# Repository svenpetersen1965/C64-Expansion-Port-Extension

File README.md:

This is an extension cable thing for the C64 Expansion Port, consisting of two PCBs, one fits into the C64, the other provices an expansion port connector, which are connected via a ribbon cable. 

Rev. 0 of this project is now built and tested. A 25cm ribbon cable is good, a 100cm ribbon cable is too long.

For User Port and Cassette Port Extension Cable see: <a href="https://github.com/svenpetersen1965/Commodore-Port-Breakout">Commodore Port Breakout</a>

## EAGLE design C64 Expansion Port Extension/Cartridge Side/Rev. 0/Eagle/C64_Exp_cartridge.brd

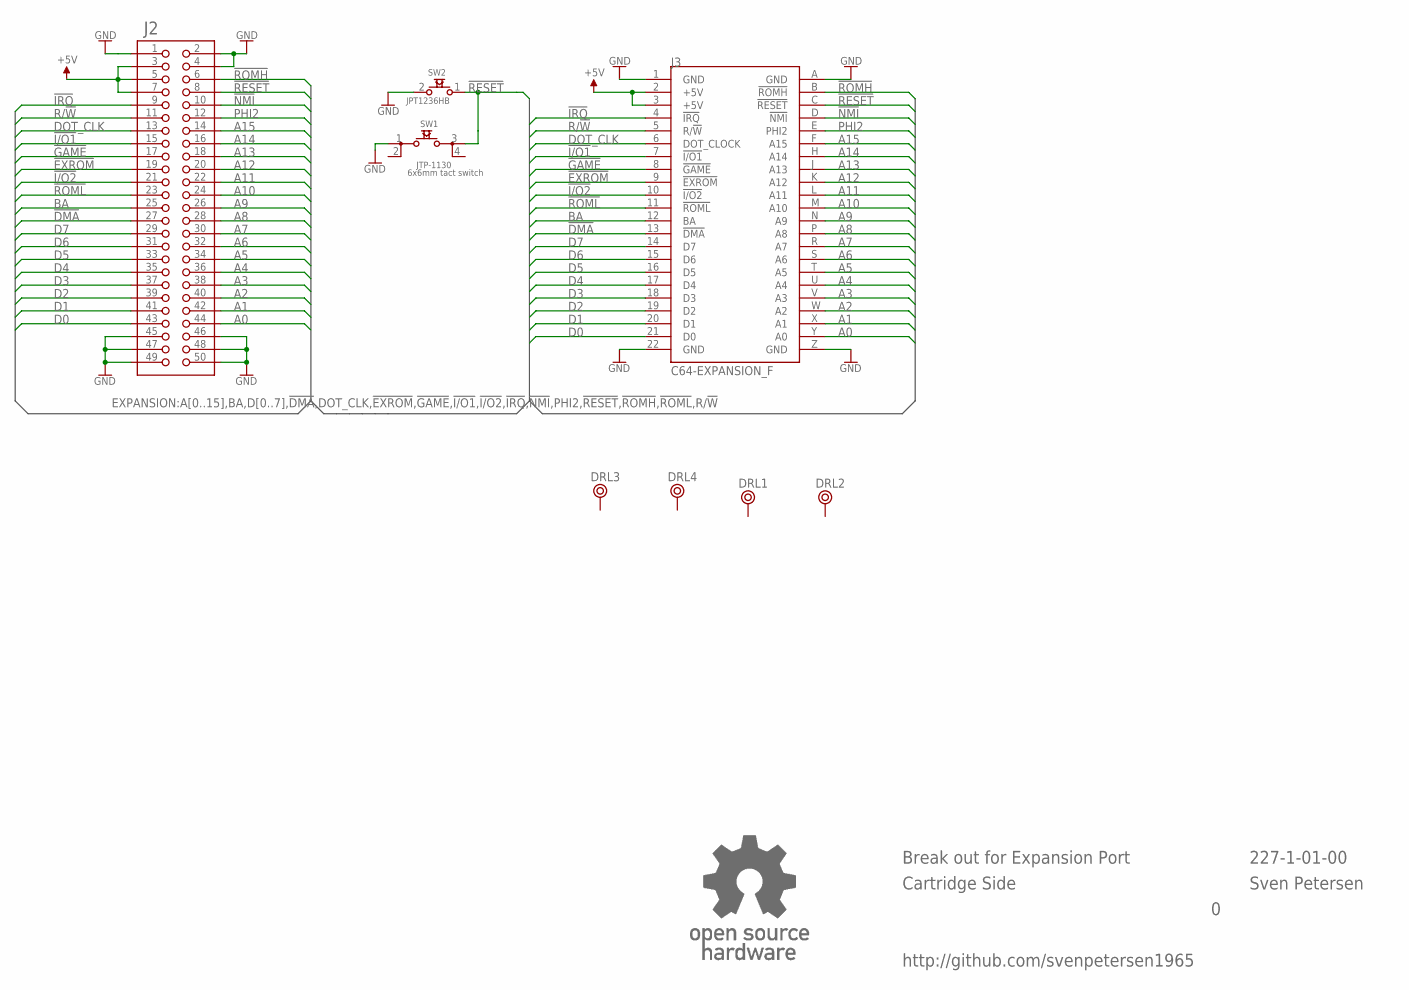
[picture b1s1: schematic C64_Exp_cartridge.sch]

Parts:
DRL1, DRL2, DRL3, DRL4: BOHR3,3
J2: PINHD-2X25BOX; 2X25WV
J3: C64-EXPANSION_F; EXPANSION_OUT
SW1: JTP-1130
SW2: JPT1236HB; JTP_1236HB
U$22: OPEN_SOURCE_HW; OPENHW

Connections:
!DMA: J2.27, J3.13 (!DMA)
!EXROM: J2.19, J3.9 (!EXROM)
!GAME: J2.17, J3.8 (!GAME)
!I/O1: J2.15, J3.7 (!I/O1)
!I/O2: J2.21, J3.10 (!I/O2)
!IRQ: J2.9, J3.4 (!IRQ)
!NMI: J2.10, J3.D (!NMI)
!RESET: J2.8, J3.C (!RESET), SW1.3, SW2.1
!ROMH: J2.6, J3.B (!ROMH)
!ROML: J2.23, J3.11 (!ROML)
+5V: J2.3, J2.5, J2.7, J3.2 (+5V), J3.3 (+5V)
A0: J2.44, J3.Y (A0)
A1: J2.42, J3.X (A1)
A2: J2.40, J3.W (A2)
A3: J2.38, J3.V (A3)
A4: J2.36, J3.U (A4)
A5: J2.34, J3.T (A5)
A6: J2.32, J3.S (A6)
A7: J2.30, J3.R (A7)
A8: J2.28, J3.P (A8)
A9: J2.26, J3.N (A9)
A10: J2.24, J3.M (A10)
A11: J2.22, J3.L (A11)
A12: J2.20, J3.K (A12)
A13: J2.18, J3.J (A13)
A14: J2.16, J3.H (A14)
A15: J2.14, J3.F (A15)
BA: J2.25, J3.12 (BA)
D0: J2.43, J3.21 (D0)
D1: J2.41, J3.20 (D1)
D2: J2.39, J3.19 (D2)
D3: J2.37, J3.18 (D3)
D4: J2.35, J3.17 (D4)
D5: J2.33, J3.16 (D5)
D6: J2.31, J3.15 (D6)
D7: J2.29, J3.14 (D7)
DOT_CLK: J2.13, J3.6 (DOT_CLOCK)
GND: J2.1, J2.2, J2.4, J2.45, J2.46, J2.47, J2.48, J2.49, J2.50, J3.1 (GND), J3.22 (GND), J3.A (GND), J3.Z (GND), SW1.1, SW2.2
PHI2: J2.12, J3.E (PHI2)
R/!W: J2.11, J3.5 (R/!W)

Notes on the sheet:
Sven Petersen
227-1-01-00
http://github.com/svenpetersen1965
6x6mm tact switch
Break out for Expansion Port
Cartridge Side

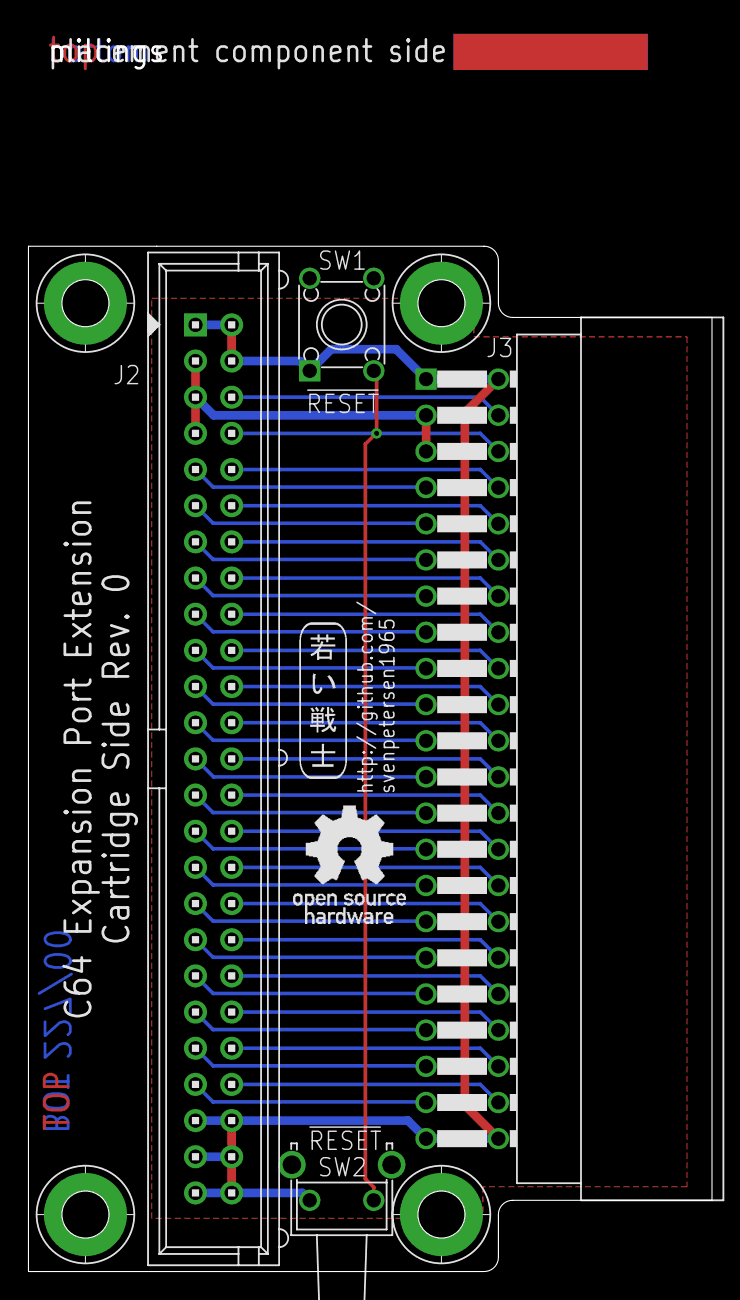
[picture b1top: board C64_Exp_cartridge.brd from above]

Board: 2 copper layers, 47.9 x 87.2 mm, 12 parts (0 on the bottom side), 40 nets.

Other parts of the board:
U$20: 2LAYER
U$21: PCB-TITLE/
U$23: SVEN_TAG

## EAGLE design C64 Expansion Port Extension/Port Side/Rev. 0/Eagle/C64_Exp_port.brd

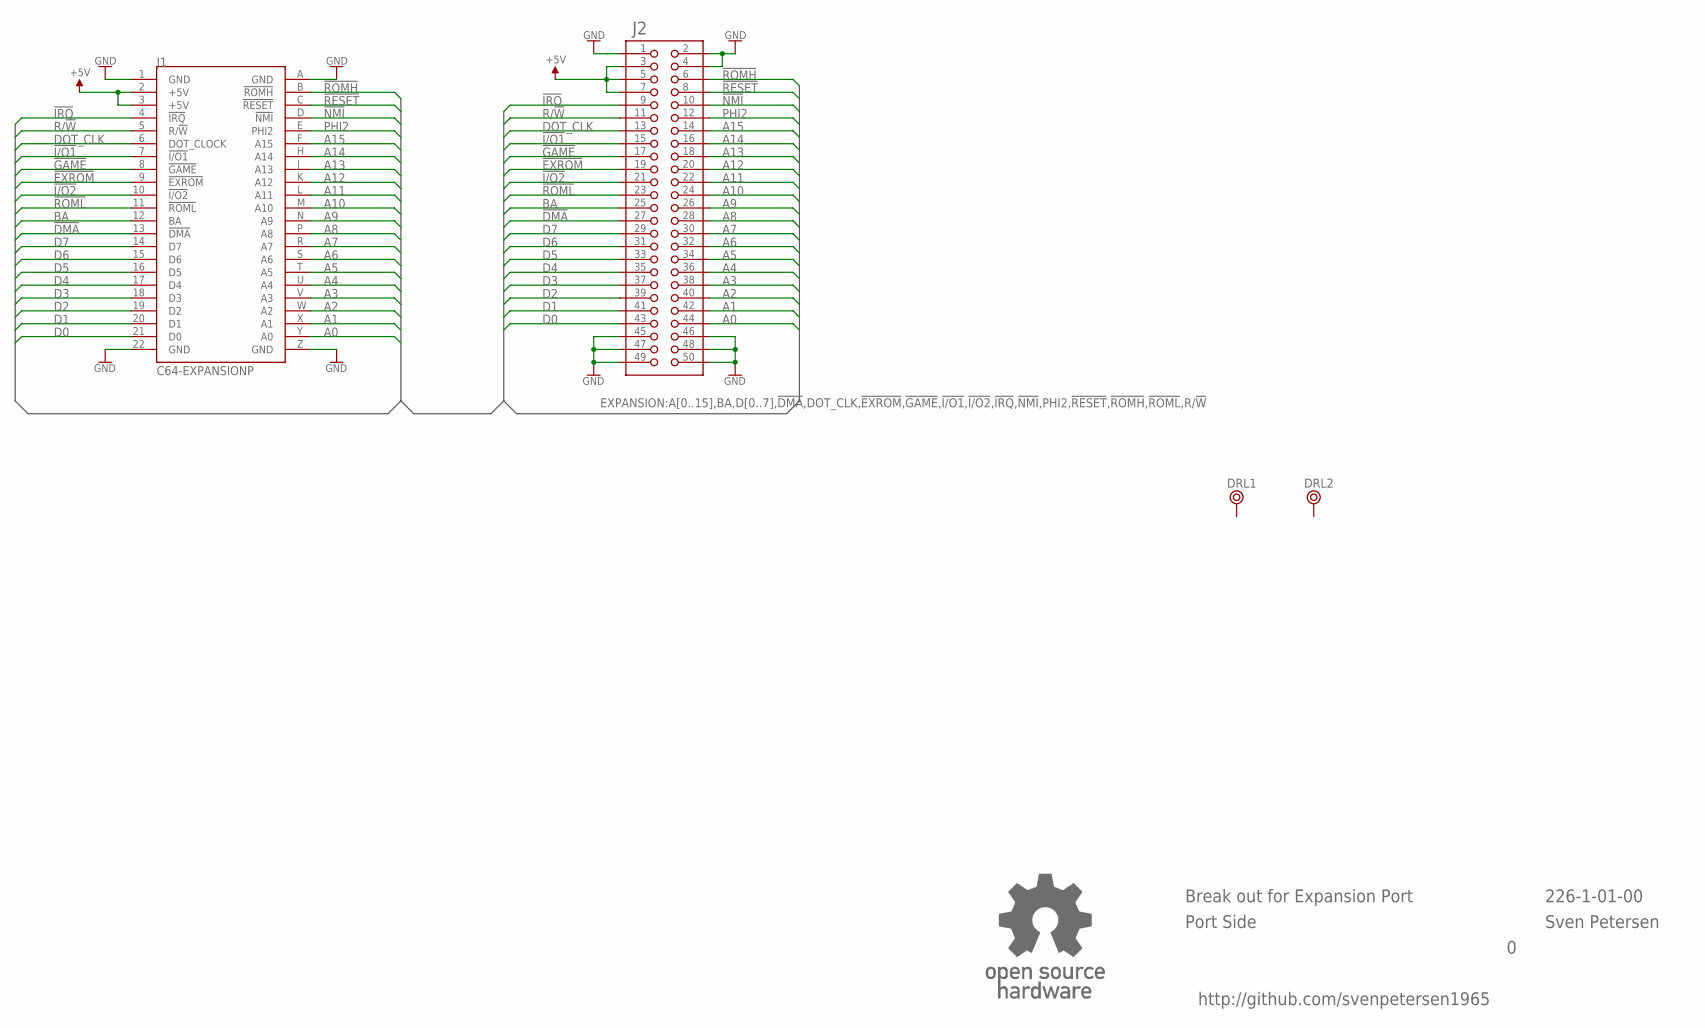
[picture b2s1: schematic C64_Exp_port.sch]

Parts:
DRL1, DRL2: BOHR3,3
J1: C64-EXPANSIONP; EXPPORT
J2: PINHD-2X25BOX; 2X25WV
U$22: OPEN_SOURCE_HW; OPENHW

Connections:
!DMA: J1.13 (!DMA), J2.27
!EXROM: J1.9 (!EXROM), J2.19
!GAME: J1.8 (!GAME), J2.17
!I/O1: J1.7 (!I/O1), J2.15
!I/O2: J1.10 (!I/O2), J2.21
!IRQ: J1.4 (!IRQ), J2.9
!NMI: J1.D (!NMI), J2.10
!RESET: J1.C (!RESET), J2.8
!ROMH: J1.B (!ROMH), J2.6
!ROML: J1.11 (!ROML), J2.23
+5V: J1.2 (+5V), J1.3 (+5V), J2.3, J2.5, J2.7
A0: J1.Y (A0), J2.44
A1: J1.X (A1), J2.42
A2: J1.W (A2), J2.40
A3: J1.V (A3), J2.38
A4: J1.U (A4), J2.36
A5: J1.T (A5), J2.34
A6: J1.S (A6), J2.32
A7: J1.R (A7), J2.30
A8: J1.P (A8), J2.28
A9: J1.N (A9), J2.26
A10: J1.M (A10), J2.24
A11: J1.L (A11), J2.22
A12: J1.K (A12), J2.20
A13: J1.J (A13), J2.18
A14: J1.H (A14), J2.16
A15: J1.F (A15), J2.14
BA: J1.12 (BA), J2.25
D0: J1.21 (D0), J2.43
D1: J1.20 (D1), J2.41
D2: J1.19 (D2), J2.39
D3: J1.18 (D3), J2.37
D4: J1.17 (D4), J2.35
D5: J1.16 (D5), J2.33
D6: J1.15 (D6), J2.31
D7: J1.14 (D7), J2.29
DOT_CLK: J1.6 (DOT_CLOCK), J2.13
GND: J1.1 (GND), J1.22 (GND), J1.A (GND), J1.Z (GND), J2.1, J2.2, J2.4, J2.45, J2.46, J2.47, J2.48, J2.49, J2.50
PHI2: J1.E (PHI2), J2.12
R/!W: J1.5 (R/!W), J2.11

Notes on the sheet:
Break out for Expansion Port
Sven Petersen
226-1-01-00
http://github.com/svenpetersen1965
Port Side

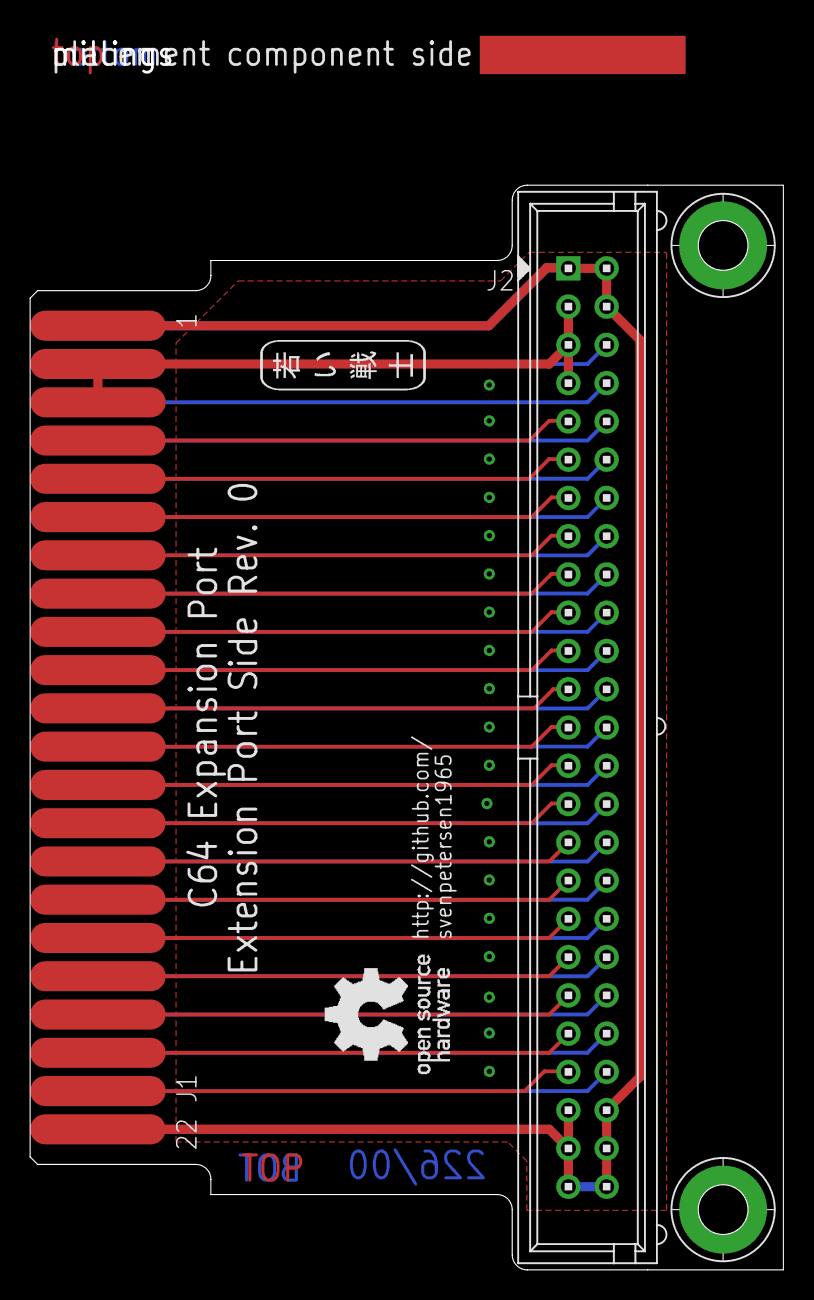
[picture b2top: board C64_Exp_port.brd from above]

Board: 2 copper layers, 49.9 x 82.2 mm, 8 parts (0 on the bottom side), 40 nets.

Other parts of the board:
U$20: 2LAYER
U$21: PCB-TITLE/
U$23: SVEN_TAG

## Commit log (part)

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2026-05-25 Create LICENSE
2026-05-25 Preliminary Release
